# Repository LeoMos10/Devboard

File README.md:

# Devboard

Devboard is a custom Raspberry Pi RP2354B development board based on the [Hack Club devboard guide](https://stasis.hackclub.com/starter-projects/devboard). The schematic and PCB are being designed in KiCad.

## Why this board?

I wanted to design a microcontroller board itself, with USB-C, GPIO, onboard buttons and status LEDs.

## Parts

- Raspberry Pi RP2354B microcontroller
- USB-C connector
- 3.3 V power supply with an inductor and a Schottky diode
- Yellow  LED and a RGB LED
- BOOTSEL, RUN and 2 user buttons
- 2.54 mm pin headers, plus additional headers, SWD debug probe

## CAD Model
No case yet.

## PCB

The KiCad project is in [`PCB/`](PCB/). Open the [KiCad project](PCB/devboard.kicad_pro) to view the schematic and board together. Custom footprints and 3D models are stored beside the KiCad files.

### Schematic

The current schematic includes the RP2354B circuit, USB-C, power, buttons and LEDs.

[Pinout](PCB/devboard_pinout.svg)

### Board

The schematic now matches the PCB references, footprints and electrical nets. Assembly files still need to be checked before ordering.

Front and rear of the PCB:

Copper layers:

## Firmware Overview

Firmware has not been added yet.

## BOM

The [BOM for one board](BOM.csv) includes JLCPCB links and the quantities in the saved parts cart. It is a design BOM; the JLCPCB assembly BOM and placement file are still pending.

## AI usage

AI assistance was used for parts research(both selcetin what component and find th ecorrect one on sites),also for KiCad advice. The schematic, footprint and PCB still was done by hand by me.

## Extra stuff
Its questionable to me too

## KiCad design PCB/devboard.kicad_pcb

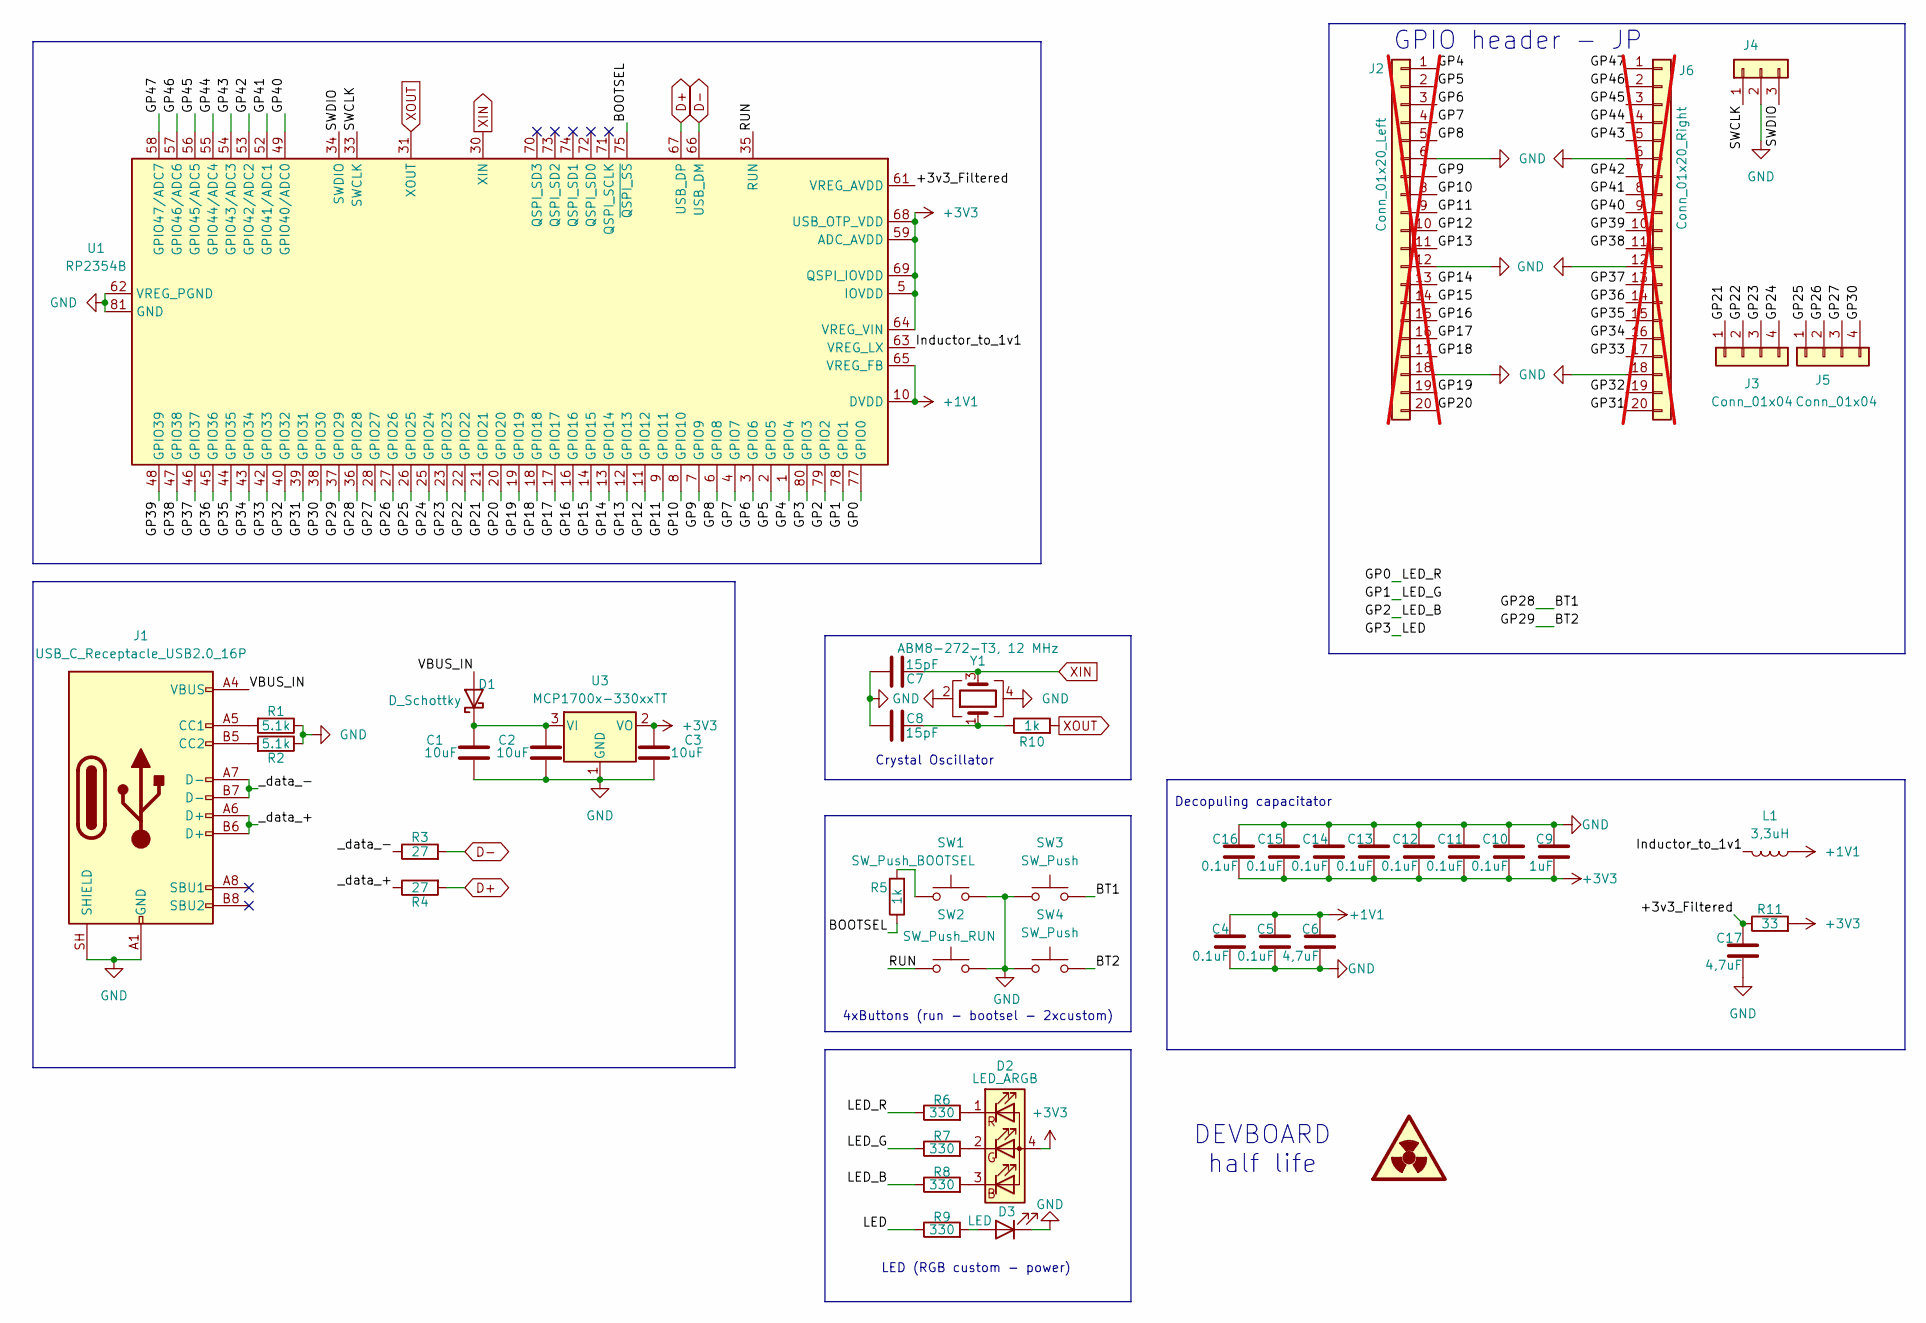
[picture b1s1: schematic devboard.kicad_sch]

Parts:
C1, C2, C3: 10uF; C_0603_1608Metric
C4, C5, C10, C11, C12, C13, C14, C15, C16: 0.1uF; C_0402_1005Metric
C6, C17: 4,7uF; C_0603_1608Metric
C7, C8: 15pF; C_0402_1005Metric
C9: 1uF; C_0402_1005Metric
D1: D_Schottky; D_SOD-123
D2: LED_ARGB; LED-ARRAY-SMD_4P-L3.2-W2.7-TL-RD_TJ-S3528
D3: LED; LED_0805_2012Metric
J1: USB_C_Receptacle_USB2.0_16P; USB_C_Receptacle_HRO_TYPE-C-31-M-12
J2: Conn_01x20_Left; goood_PinHeader_1x20_P2.54mm_Vertical_left_cutom_pad; not fitted
J3, J5: Conn_01x04; PinHeader_1x04_P2.54mm_Vertical
J4: Conn_01x03; PinHeader_1x03_P2.54mm_Vertical
J6: Conn_01x20_Right; goood_PinHeader_1x20_P2.54mm_Vertical_right_cutom_pad; not fitted
L1: 3,3uH; IND-SMD_L2.0-W1.6_AOTA-B201610S3R3-101-T
R1, R2: 5.1k; R_0402_1005Metric
R3, R4: 27; R_0402_1005Metric
R5, R10: 1k; R_0402_1005Metric
R6, R7, R8, R9: 330; R_0402_1005Metric
R11: 33; R_0402_1005Metric
SW1: SW_Push_BOOTSEL; SW_SPST_TS-1088-xR020
SW2: SW_Push_RUN; SW_SPST_TS-1088-xR020
SW3, SW4: SW_Push; SW_SPST_TS-1088-xR020
U1: RP2354B; QFN-80-1EP_10x10mm_P0.4mm_EP3.4x3.4mm
U3: MCP1700x-330xxTT; SOT-23
Y1: ABM8-272-T3, 12 MHz; Crystal_SMD_3225-4Pin_3.2x2.5mm

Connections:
+1V1: C4.1, C5.1, C6.1, L1.1, U1.10 (DVDD), U1.32 (DVDD), U1.51 (DVDD), U1.65 (VREG_FB)
+3V3: C3.1, C9.2, C10.2, C11.2, C12.2, C13.2, C14.2, C15.2, C16.2, D2.4 (A), R11.2, U1.5 (IOVDD), U1.15 (IOVDD), U1.24 (IOVDD), U1.29 (IOVDD), U1.41 (IOVDD), U1.50 (IOVDD), U1.59 (ADC_AVDD), U1.60 (IOVDD), U1.64 (VREG_VIN), U1.68 (USB_OTP_VDD), U1.69 (QSPI_IOVDD), U1.76 (IOVDD), U3.2 (VO)
/+3v3_Filtered: C17.1, R11.1, U1.61 (VREG_AVDD)
/BOOTSEL: R5.1, U1.75 (~QSPI_SS)
/BT1: SW3.2, U1.36 (GPIO28)
/BT2: SW4.2, U1.37 (GPIO29)
/GP0: R6.1, U1.77 (GPIO0)
/GP1: R7.1, U1.78 (GPIO1)
/GP2: R8.1, U1.79 (GPIO2)
/GP3: R9.1, U1.80 (GPIO3)
/GP4: J2.1, U1.1 (GPIO4)
/GP5: J2.2, U1.2 (GPIO5)
/GP6: J2.3, U1.3 (GPIO6)
/GP7: J2.4, U1.4 (GPIO7)
/GP8: J2.5, U1.6 (GPIO8)
/GP9: J2.7, U1.7 (GPIO9)
/GP10: J2.8, U1.8 (GPIO10)
/GP11: J2.9, U1.9 (GPIO11)
/GP12: J2.10, U1.11 (GPIO12)
/GP13: J2.11, U1.12 (GPIO13)
/GP14: J2.13, U1.13 (GPIO14)
/GP15: J2.14, U1.14 (GPIO15)
/GP16: J2.15, U1.16 (GPIO16)
/GP17: J2.16, U1.17 (GPIO17)
/GP18: J2.17, U1.18 (GPIO18)
/GP19: J2.19, U1.19 (GPIO19)
/GP20: J2.20, U1.20 (GPIO20)
/GP21: J3.1, U1.21 (GPIO21)
/GP22: J3.2, U1.22 (GPIO22)
/GP23: J3.3, U1.23 (GPIO23)
/GP24: J3.4, U1.25 (GPIO24)
/GP25: J5.1, U1.26 (GPIO25)
/GP26: J5.2, U1.27 (GPIO26)
/GP27: J5.3, U1.28 (GPIO27)
/GP30: J5.4, U1.38 (GPIO30)
/GP31: J6.20, U1.39 (GPIO31)
/GP32: J6.19, U1.40 (GPIO32)
/GP33: J6.17, U1.42 (GPIO33)
/GP34: J6.16, U1.43 (GPIO34)
/GP35: J6.15, U1.44 (GPIO35)
/GP36: J6.14, U1.45 (GPIO36)
/GP37: J6.13, U1.46 (GPIO37)
/GP38: J6.11, U1.47 (GPIO38)
/GP39: J6.10, U1.48 (GPIO39)
/GP40: J6.9, U1.49 (GPIO40/ADC0)
/GP41: J6.8, U1.52 (GPIO41/ADC1)
/GP42: J6.7, U1.53 (GPIO42/ADC2)
/GP43: J6.5, U1.54 (GPIO43/ADC3)
/GP44: J6.4, U1.55 (GPIO44/ADC4)
/GP45: J6.3, U1.56 (GPIO45/ADC5)
/GP46: J6.2, U1.57 (GPIO46/ADC6)
/GP47: J6.1, U1.58 (GPIO47/ADC7)
/Inductor_to_1v1: L1.2, U1.63 (VREG_LX)
/RUN: SW2.1, U1.35 (RUN)
/SWCLK: J4.1, U1.33 (SWCLK)
/SWDIO: J4.3, U1.34 (SWDIO)
/VBUS_IN: D1.2 (A), J1.A4 (VBUS), J1.A9 (VBUS), J1.B4 (VBUS), J1.B9 (VBUS)
/_data_+: J1.A6 (D+), J1.B6 (D+), R4.1
/_data_-: J1.A7 (D-), J1.B7 (D-), R3.1
D+: R4.2, U1.67 (USB_DP)
D-: R3.2, U1.66 (USB_DM)
GND: C1.2, C2.2, C3.2, C4.2, C5.2, C6.2, C7.1, C8.1, C9.1, C10.1, C11.1, C12.1, C13.1, C14.1, C15.1, C16.1, C17.2, D3.1 (K), J1.A1 (GND), J1.A12 (GND), J1.B1 (GND), J1.B12 (GND), J1.SH (SHIELD), J2.6, J2.12, J2.18, J4.2, J6.6, J6.12, J6.18, R1.1, R2.1, SW1.2, SW2.2, SW3.1, SW4.1, U1.62 (VREG_PGND), U1.81 (GND), U3.1 (GND), Y1.2, Y1.4
unnamed: C8.2, R10.1, Y1.1
unnamed: C1.1, C2.1, D1.1 (K), U3.3 (VI)
unnamed: D2.3 (BK), R8.2
unnamed: D2.1 (GK), R6.2
unnamed: D2.2 (RK), R7.2
unnamed: D3.2 (A), R9.2
unnamed: J1.A5 (CC1), R1.2
unnamed: J1.B5 (CC2), R2.2
unnamed: R5.2, SW1.1
XIN: C7.2, U1.30 (XIN), Y1.3
XOUT: R10.2, U1.31 (XOUT)

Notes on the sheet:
4xButtons (run - bootsel - 2xcustom)
DEVBOARD half life
GPIO header - JP
Decopuling capacitator
Crystal Oscillator
LED (RGB custom - power)

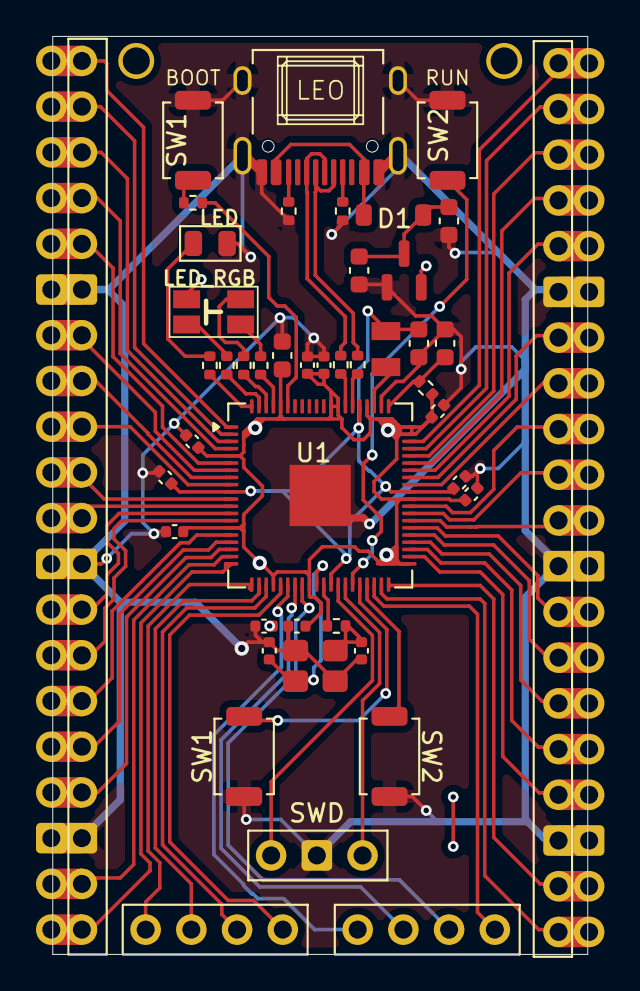
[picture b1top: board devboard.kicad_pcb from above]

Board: 2 copper layers, 29.7 x 51.0 mm, 45 parts (0 on the bottom side), 73 nets.

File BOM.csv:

References,Qty per board,Value,MFR Part #,Footprint (schematic),JLCPCB Part #,Cart Qty,JLCPCB Link,Cart check,Assembly
U1,1,RP2354B,RP2354B,Package_DFN_QFN:QFN-80-1EP_10x10mm_P0.4mm_EP3.4x3.4mm,C39843328,2,https://jlcpcb.com/partdetail/C39843328,One spare in cart,PCBA
U3,1,3.3V LDO,MCP1700T-3302E/TT,Package_TO_SOT_SMD:SOT-23,C39051,1,https://jlcpcb.com/partdetail/C39051,Matched,PCBA
J1,1,USB-C,TYPE-C-31-M-12,Connector_USB:USB_C_Receptacle_HRO_TYPE-C-31-M-12,C165948,1,https://jlcpcb.com/partdetail/C165948,Matched,PCBA
L1,1,3.3uH,AOTA-B201610S3R3-101-T,EasyEDA_Imported:IND-SMD_L2.0-W1.6_AOTA-B201610S3R3-101-T,C42411119,1,https://jlcpcb.com/partdetail/AbraconLLC-AOTA_B201610S3R3_10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,Quantity matched; availability reported unavailable,PCBA
D1,1,Schottky diode,B5819W SL,Diode_SMD:D_SOD-123,C8598,1,https://jlcpcb.com/partdetail/C8598,Matched,PCBA
D2,1,RGB LED common anode,TJ-S3528UG2W9TLCCYRGB-A5,EasyEDA_Imported:LED-ARRAY-SMD_4P-L3.2-W2.7-TL-RD_TJ-S3528,C601699,1,https://jlcpcb.com/partdetail/C601699,Matched,PCBA
D3,1,Yellow LED,KT-0805Y,LED_SMD:LED_0805_2012Metric,C2296,1,https://jlcpcb.com/partdetail/C2296,Matched,PCBA
Y1,1,12MHz crystal,ABM8-272-T3,Crystal:Crystal_SMD_3225-4Pin_3.2x2.5mm,C20625731,1,https://jlcpcb.com/partdetail/C20625731,Matched,PCBA
"SW1,SW2,SW3,SW4",4,Push button,TS-1088-AR02016,Button_Switch_SMD:SW_SPST_TS-1088-xR020,C720477,4,https://jlcpcb.com/partdetail/C720477,Matched,PCBA
"C1,C2,C3",3,10uF,CL10A106KP8NNNC,Capacitor_SMD:C_0603_1608Metric,C19702,3,https://jlcpcb.com/partdetail/C19702,Matched,PCBA
"C7,C8",2,15pF,0402CG150J500NT,Capacitor_SMD:C_0402_1005Metric,C1548,2,https://jlcpcb.com/partdetail/C1548,Matched,PCBA
"C4,C5,C10,C11,C12,C13,C14,C15,C16",9,100nF,CL05B104KO5NNNC,Capacitor_SMD:C_0402_1005Metric,C1525,9,https://jlcpcb.com/partdetail/C1525,Matched,PCBA
"C6,C17",2,4.7uF,CL10A475KO8NNNC,Capacitor_SMD:C_0603_1608Metric,C19666,2,https://jlcpcb.com/partdetail/C19666,Matched,PCBA
C9,1,1uF,CL05A105KA5NQNC,Capacitor_SMD:C_0402_1005Metric,C52923,1,https://jlcpcb.com/partdetail/C52923,Matched,PCBA
"R1,R2",2,5.1k,0402WGF5101TCE,Resistor_SMD:R_0402_1005Metric,C25905,2,https://jlcpcb.com/partdetail/C25905,Matched,PCBA
"R3,R4",2,27R,0402WGF270JTCE,Resistor_SMD:R_0402_1005Metric,C25100,2,https://jlcpcb.com/partdetail/25843-0402WGF270JTCE/C25100,Quantity matched; availability reported unavailable,PCBA
"R5,R10",2,1k,0402WGF1001TCE,Resistor_SMD:R_0402_1005Metric,C11702,2,https://jlcpcb.com/partdetail/C11702,Matched,PCBA
"R6,R7,R8,R9",4,330R,0402WGF3300TCE,Resistor_SMD:R_0402_1005Metric,C25104,4,https://jlcpcb.com/partdetail/C25104,Matched,PCBA
R11,1,33R,0402WGF330JTCE,Resistor_SMD:R_0402_1005Metric,C25105,1,https://jlcpcb.com/partdetail/C25105,Matched,PCBA
J2,1,1x20 pin header 2.54mm,,leo/kicad_vari:goood_PinHeader_1x20_P2.54mm_Vertical_left_cutom_pad,,0,,Not in cart,Hand solder
J6,1,1x20 pin header 2.54mm,,leo/kicad_vari:goood_PinHeader_1x20_P2.54mm_Vertical_right_cutom_pad,,0,,Not in cart,Hand solder
"J3,J5",2,1x04 pin header 2.54mm,,Connector_PinHeader_2.54mm:PinHeader_1x04_P2.54mm_Vertical,,0,,Not in cart,Hand solder
J4,1,1x03 pin header 2.54mm,,Connector_PinHeader_2.54mm:PinHeader_1x03_P2.54mm_Vertical,,0,,Not in cart,Hand solder
